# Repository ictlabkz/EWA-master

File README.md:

# EWA
EWA (Environment with Application) - open source project for measure of environment (weather stratosphere and troposphere) on Arduino Platform and send data from sensors in 3G networks to Control Panel.

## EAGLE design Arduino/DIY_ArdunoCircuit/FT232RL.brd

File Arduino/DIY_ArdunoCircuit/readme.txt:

.lay .brd .srh .sch

Список деталей для сборки Z-DIYino FT232RL

1 x Кусок текстолита (80х65мм)

1 x Микроконтроллер ATmega8/168/328 (DIP)
1 x Микросхема FT232RL (SMD)
1 x Стабилизатор 7805/КР142ЕН5А (DIP)
1 x Стабилизатор ASM1117 3.3 (SMD)

1 x Диод 1N4007/M7 (SMD) 
6 x Резисторы 1 кОм (SMD 1206)
1 x Резисторы 10 кОм (SMD 1206)
2 x Конденсатор керамический 22пФ (SMD 1206)
4 x Конденсатор керамический 0.1мкФ (SMD 1206)
2 x Конденсатор элетролитический 100мкФ х 16В (DIP низкие) 
4 x Светодиоды 3мм любого цвета (DIP)
1 x Кварц 16 МГц (DIP)

1 x Панелька DIP28 (узкая)
1 x Джампер 2.54мм 
1 x Разъем питания 5.5 х 2.1мм 
1 x Кнопка тактовая четырех контактная 6 мм 
2 x Гребенка 2.54мм "мама" 6pin  
2 x Гребенка 2.54мм "мама" 8pin  
2 x Гребенка 2.54мм "папа" 40pin 

P.S. Если не найдете, гребенки 6 и 8pin, то берите 40pin и распилите на необходимые части

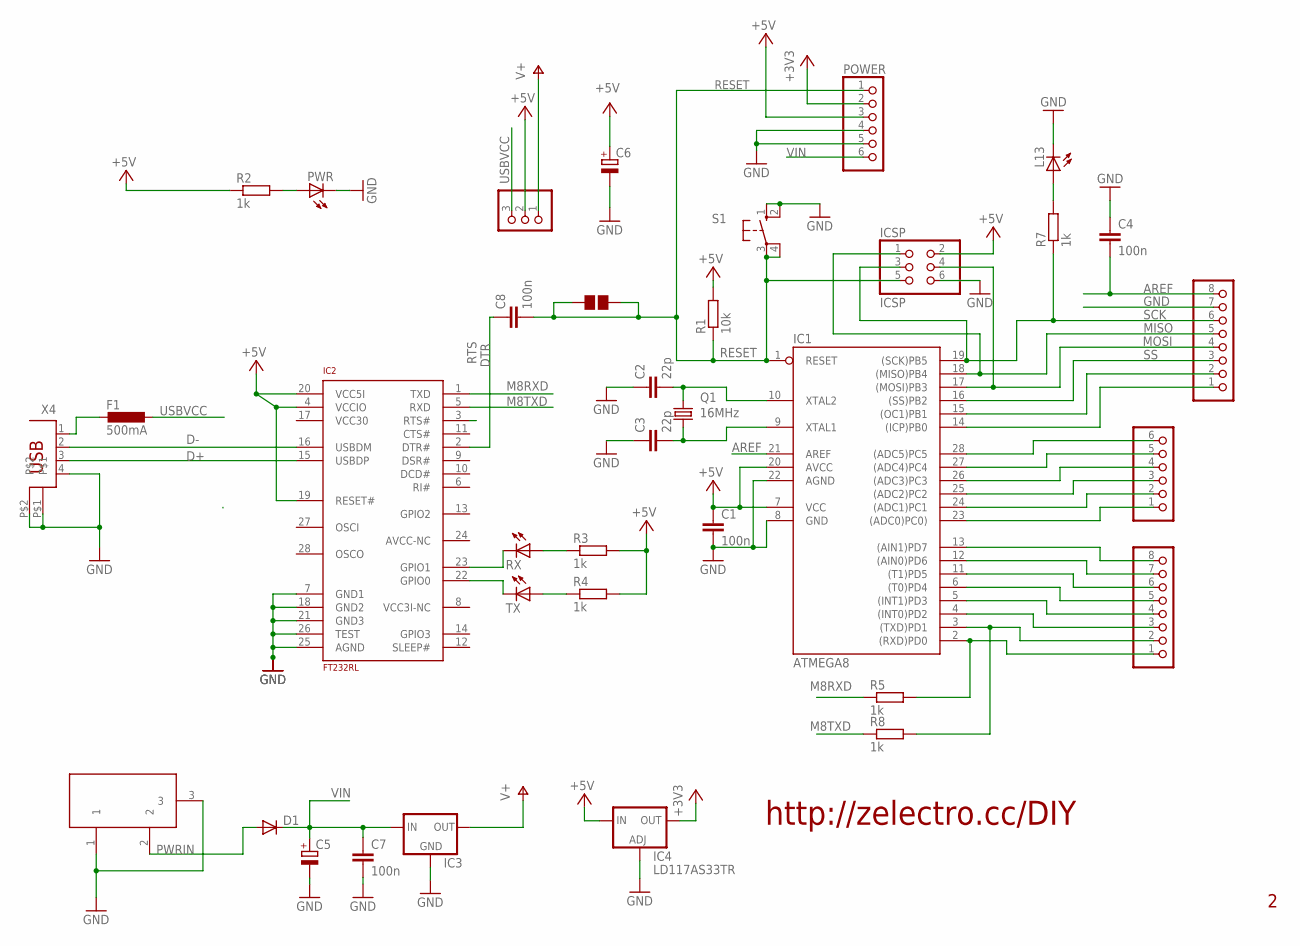
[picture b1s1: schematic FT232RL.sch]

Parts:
C1, C4, C7, C8: 100n; C1206K
C2, C3: 22p; C1206K
C5, C6: CPOL-EUE2.5-7; E2,5-7
D1: DIODE-SMB; SMB
F1: 500mA; L1812
IC1: ATMEGA8; DIL28-3
IC2: FT232RL; SSOP28
IC3: 78XXL
IC4: LD117AS33TR; SOT223
ICSP: ICSP; 2X03
J1, J3: PINHD-1X8; 1X08
J2: PINHD-1X6; 1X06
JP3: PINHD-1X3; 1X03
L13: LED3MM
POWER: PINHD-1X6; 1X06
PWR: LED3MM
Q1: 16MHz; HC49/S
R1: 10k; M1406
R2, R3, R4, R5, R7, R8: 1k; M1406
RX: LED3MM
S1: 10-XX; B3F-10XX
TX: LED3MM
X2: DC21MMX; DC-21MM
X4: PN61729

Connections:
+3V3: IC4.4 (OUT), POWER.2
+5V: C1.1, C6.+, IC1.7 (VCC), IC1.20 (AVCC), IC2.4 (VCCIO), IC2.19 (RESET#), IC2.20 (VCC5I), IC4.3 (IN), ICSP.2, JP3.2, POWER.3, R1.2, R2.1, R3.2, R4.2
AREF: C4.2, IC1.21 (AREF), J3.8
D+: IC2.15 (USBDP), X4.3
D-: IC2.16 (USBDM), X4.2
DTR: C8.1, IC2.2 (DTR#)
GND: C1.2, C2.1, C3.1, C4.1, C5.-, C6.-, C7.2, IC1.8 (GND), IC1.22 (AGND), IC2.7 (GND1), IC2.18 (GND2), IC2.21 (GND3), IC2.25 (AGND), IC2.26 (TEST), IC3.GND, IC4.1 (ADJ), ICSP.6, J3.7, L13.K (C), POWER.4, POWER.5, PWR.K (C), S1.1 (S), S1.2 (S1), X2.1, X2.3, X4.4, X4.P$1, X4.P$2
M8RXD: IC2.1 (TXD), R5.1
M8TXD: IC2.5 (RXD), R8.1
MISO: IC1.18 ((MISO)PB4), ICSP.1, J3.5
MOSI: IC1.17 ((MOSI)PB3), ICSP.4, J3.4
unnamed: L13.A, R7.2
unnamed: PWR.A, R2.2
unnamed: IC1.14 ((ICP)PB0), J3.1
unnamed: C3.2, IC1.9 (XTAL1), Q1.1
unnamed: C2.2, IC1.10 (XTAL2), Q1.2
unnamed: F1.2, X4.1
unnamed: IC1.4 ((INT0)PD2), J1.3
unnamed: IC1.5 ((INT1)PD3), J1.4
unnamed: IC1.6 ((T0)PD4), J1.5
unnamed: IC1.11 ((T1)PD5), J1.6
unnamed: IC1.12 ((AIN0)PD6), J1.7
unnamed: IC1.13 ((AIN1)PD7), J1.8
unnamed: IC1.23 ((ADC0)PC0)), J2.1
unnamed: IC1.24 ((ADC1)PC1), J2.2
unnamed: IC1.25 ((ADC2)PC2), J2.3
unnamed: IC1.26 ((ADC3)PC3), J2.4
unnamed: IC1.27 ((ADC4)PC4), J2.5
unnamed: IC1.28 ((ADC5)PC5), J2.6
unnamed: IC1.15 ((OC1)PB1), J3.2
unnamed: IC2.23 (GPIO1), RX.K (C)
unnamed: IC2.22 (GPIO0), TX.K (C)
unnamed: R3.1, RX.A
unnamed: R4.1, TX.A
PD0: IC1.2 ((RXD)PD0), J1.1, R5.2
PD1: IC1.3 ((TXD)PD1), J1.2, R8.2
PWRIN: D1.A, X2.2
RESET: C8.2, IC1.1 (RESET), ICSP.5, POWER.1, R1.1, S1.3, S1.4 (P1)
RTS: IC2.3 (RTS#)
SCK: IC1.19 ((SCK)PB5), ICSP.3, J3.6, R7.1
SS: IC1.16 ((SS)PB2), J3.3
USBVCC: F1.1, JP3.3
V+: IC3.OUT, JP3.1
VCC30: IC2.17 (VCC30)
VIN: C5.+, C7.1, D1.C, IC3.IN, POWER.6

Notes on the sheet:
http://zelectro.cc/DIY

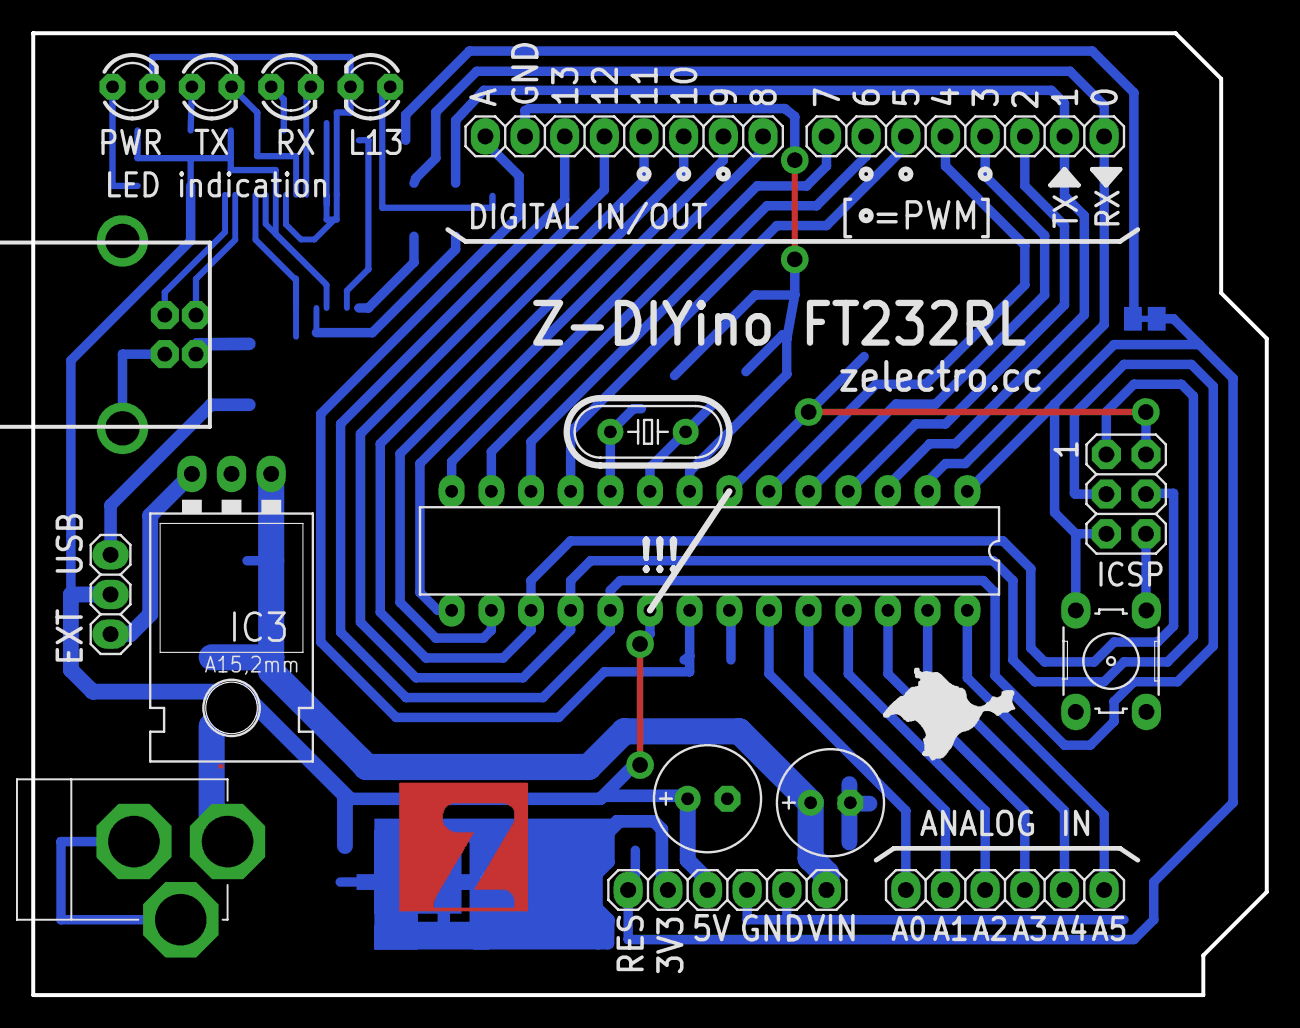
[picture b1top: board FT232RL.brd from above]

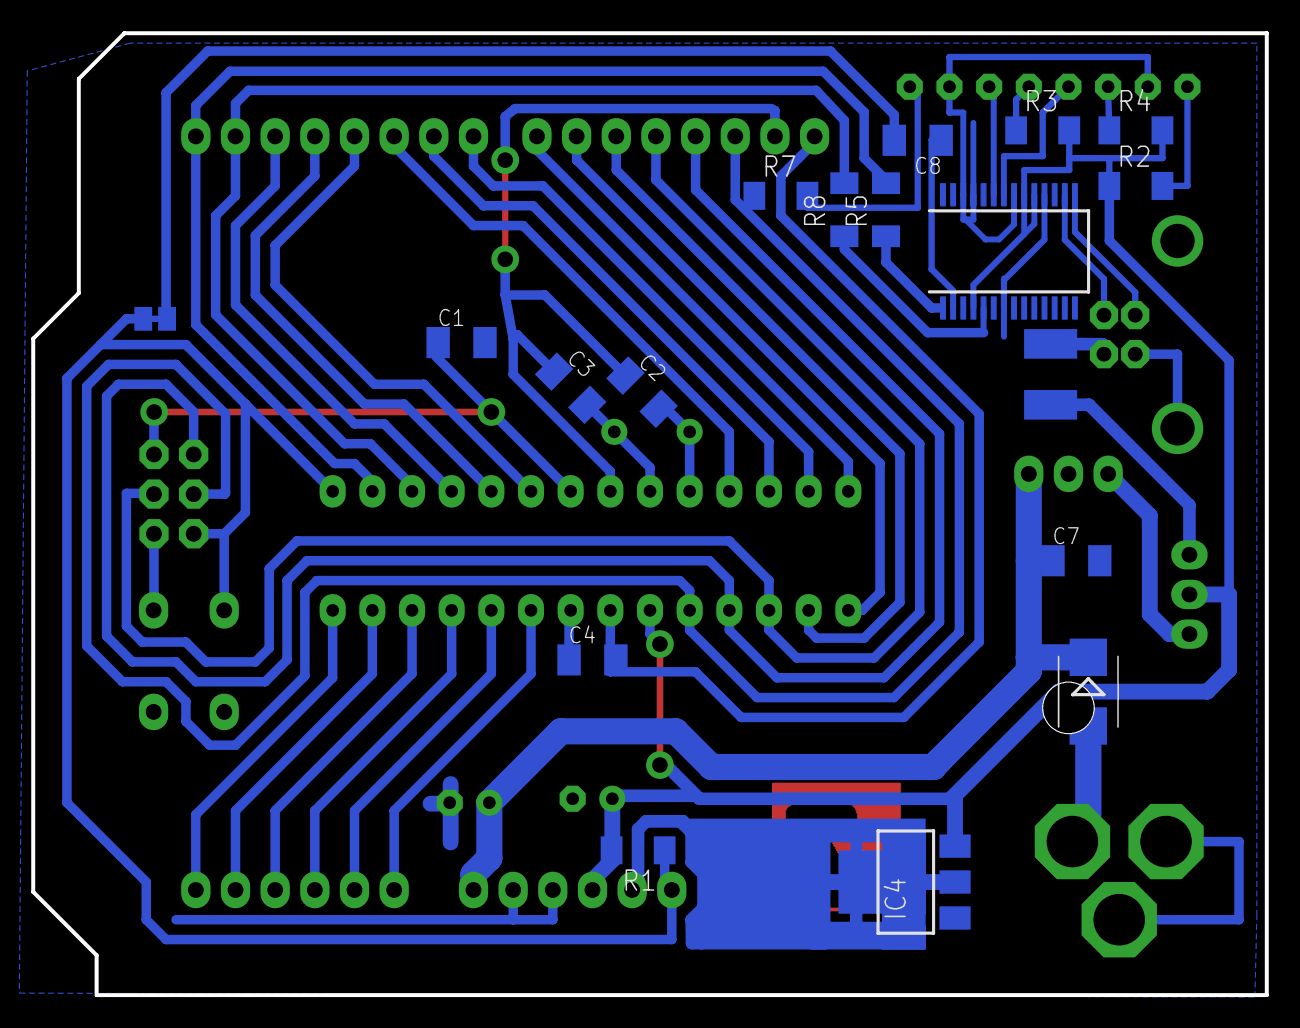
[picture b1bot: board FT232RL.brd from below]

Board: 2 copper layers, 79.0 x 61.6 mm, 35 parts (17 on the bottom side), 43 nets.
